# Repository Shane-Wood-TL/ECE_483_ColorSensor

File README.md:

A color sensor project for ECE-483 designed by Shane Wood and Simon Elliot. 
This system is powered by an ESP32-C3 and a TCS3472 running the ESP-IDF framework. A custom PCB was designed which has mounting holes and spots for the microcontroller, display, and color sensor.

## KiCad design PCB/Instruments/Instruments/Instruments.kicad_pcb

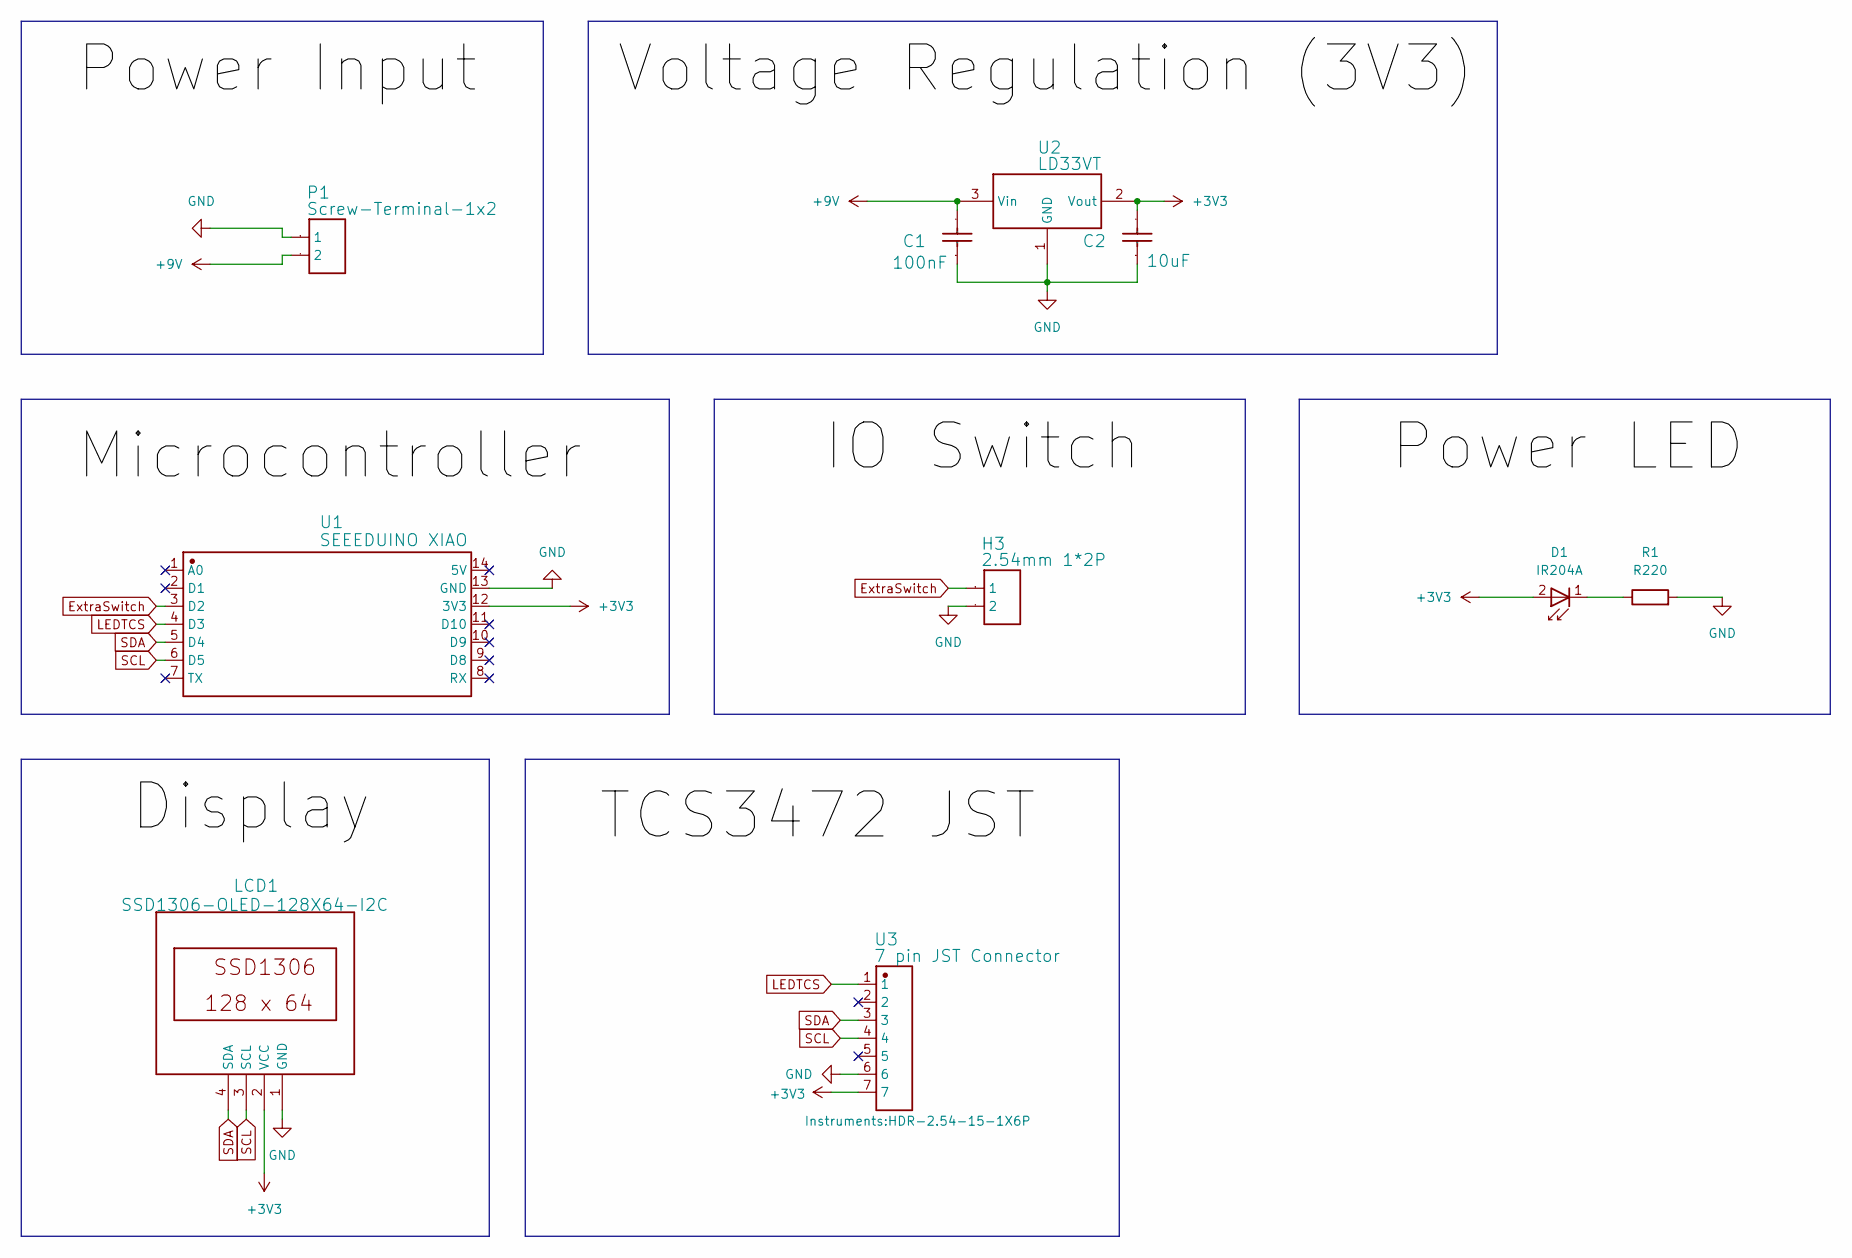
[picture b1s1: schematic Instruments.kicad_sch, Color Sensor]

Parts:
C1: 100nF; CAP-TH_L4.2-W3.8-P2.54-D0.5; Manufacturer Part CT4-0805Y104M500
C2: 10uF; CAP-TH_L4.2-W3.8-P2.54-D0.5; Manufacturer Part CT4-0805Y104M500
D1: IR204A; LED_D3.0mm_IRBlack
H3: 2.54mm 1*2P; HDR-F-2.54_1X2
LCD1: SSD1306-OLED-128X64-I2C
P1: Screw-Terminal-1x2; SCREW-TERMINAL-1X2
R1: R220; R_Array_SIP4
U1: SEEEDUINO XIAO; MODULE XAIO 14P-2.54-21X17.8MM
U2: LD33VT
U3: 7 pin JST Connector; HDR-2.54-15-1X6P

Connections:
+3V3: C2.2, D1.2 (A), LCD1.2 (VCC), U1.12 (3V3), U2.2 (Vout), U3.7
+9V: C1.2, P1.2, U2.3 (Vin)
ExtraSwitch: H3.1, U1.3 (D2)
GND: C1.1, C2.1, H3.2, LCD1.1 (GND), P1.1, R1.2, U1.13 (GND), U2.1 (GND), U3.6
LEDTCS: U1.4 (D3), U3.1
unnamed: D1.1 (K), R1.1
SCL: LCD1.3 (SCL), U1.6 (D5), U3.4
SDA: LCD1.4 (SDA), U1.5 (D4), U3.3

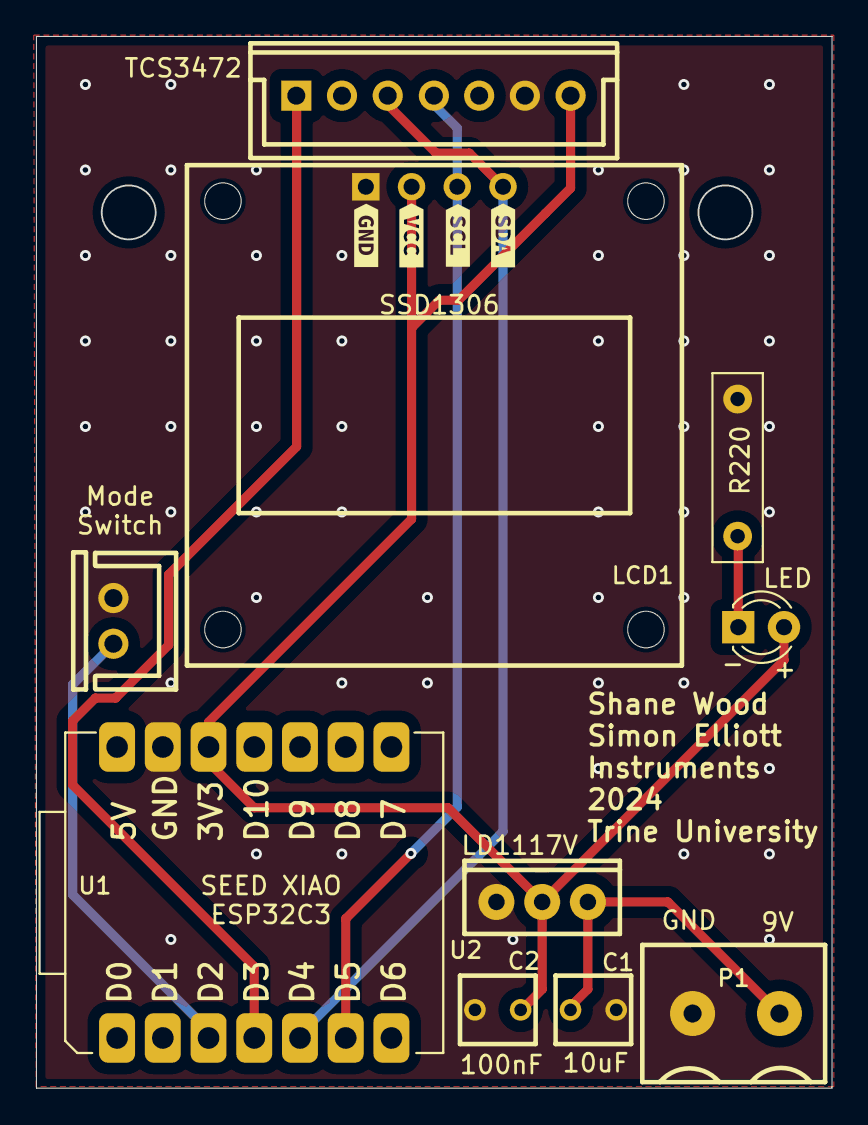
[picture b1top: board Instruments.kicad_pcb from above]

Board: 2 copper layers, 44.1 x 58.4 mm, 10 parts (0 on the bottom side), 8 nets.

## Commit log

2024-10-09 Added PCB, Code
2024-11-07 Finished Code + PCB
2024-11-08 Added font creation tool
2024-11-26 Added Labels for R, G, B for the named color mode
